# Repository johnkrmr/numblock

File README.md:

# Numblock #
A small 4x5 diy keypad to get into pcb design and custom keyboards.

## IMPORTANT ##
PCB not tested yet. There's no guarantee that it will work right now!  
Front panel needed to mount 3-pin switches. No files for that provided yet.  
Generally this README and the whole project is far away from being
complete.

## Features ##
- 4x5 keys (cherry mx compatible, hotswappable)
- compatible with variety of Adafruit ItsyBitsy boards:
	- 32u4 (3.3V 8MHz Version!)
	- M4
	- nRF52840
	- RP2040?
	- M0?
- up to 2 rotary encoders (optional)
- indicator RGB led (optional)
- RGB underglow (optional)
- RGB backlight (optional)
- i2c OLED-Display (optional)
- small 'prototyping' area with access to i2c, serial + some analog Pins

## Components ##
- PCB
- 20 1N4148W Diods (SOD123 package)
- 20 hotswap sockets for cherry mx compatible switches
- 20 cherry mx compatible switches (both 3 and 5 pin versions should
work)
- compatible ItsyBitsy controller (cf. features)
- 8 SK6812 mini *HW* RGB LEDs for underglow + top indicator led
- 20 SK6812 mini RGB LEDs for backlight
- 0.1μF 0805 capacitors for each RGB LED (cf. notes)
- up to 2 Alps EC11E rotary encoders
- i2c OLED display, [this
one](https://www.waveshare.com/wiki/0.91inch_OLED_Module) should fit perfectly
- front panel
- some sort of case or an extra back panel
- screws to hold the whole thing together
- rubber feet (otherwise typing won't be much fun)

## Notes ##
### Electronics ###
- 0.1μF capacitors are recommended according to the datasheet. There are many
designs without them. I do not know whether or not they are necessary.
- A resistor on the LED data line between the controller and the first led is
recommended. I forgot to add that on. Here as well many pcbs do not include
them. It should work. [Supposedly](https://learn.adafruit.com/adafruit-neopixel-uberguide/basic-connections) what could happen is that the first LED in the 'chain' gets fried every
once in a while.
- A wireless version could be achieved with the nRF52840 in combination with the [LiIon/LiPoly
Backpack](https://www.adafruit.com/product/2124).

### Software ###
- I experienced some form of 'ghosting' in the upper two rows when setting
columns to *high* and
reading from row pins with *internal pulldowns* (diodes
facing opposite way than shown in schematics). When holding 4
switches down in same row, the 5th one shows as constantly on or
continuously toggling. This does
not seam to appear when setting rows to *low* and reading from columns with *internal
pullups*. So I guess **use internal pullups** for scanning the matrix.

## Resources ##
- [Josef Adamcik's sofle
keyboard](https://josefadamcik.github.io/SofleKeyboard/)
- [KiCad Keyboard Tutorial](https://github.com/ruiqimao/keyboard-pcb-guide)

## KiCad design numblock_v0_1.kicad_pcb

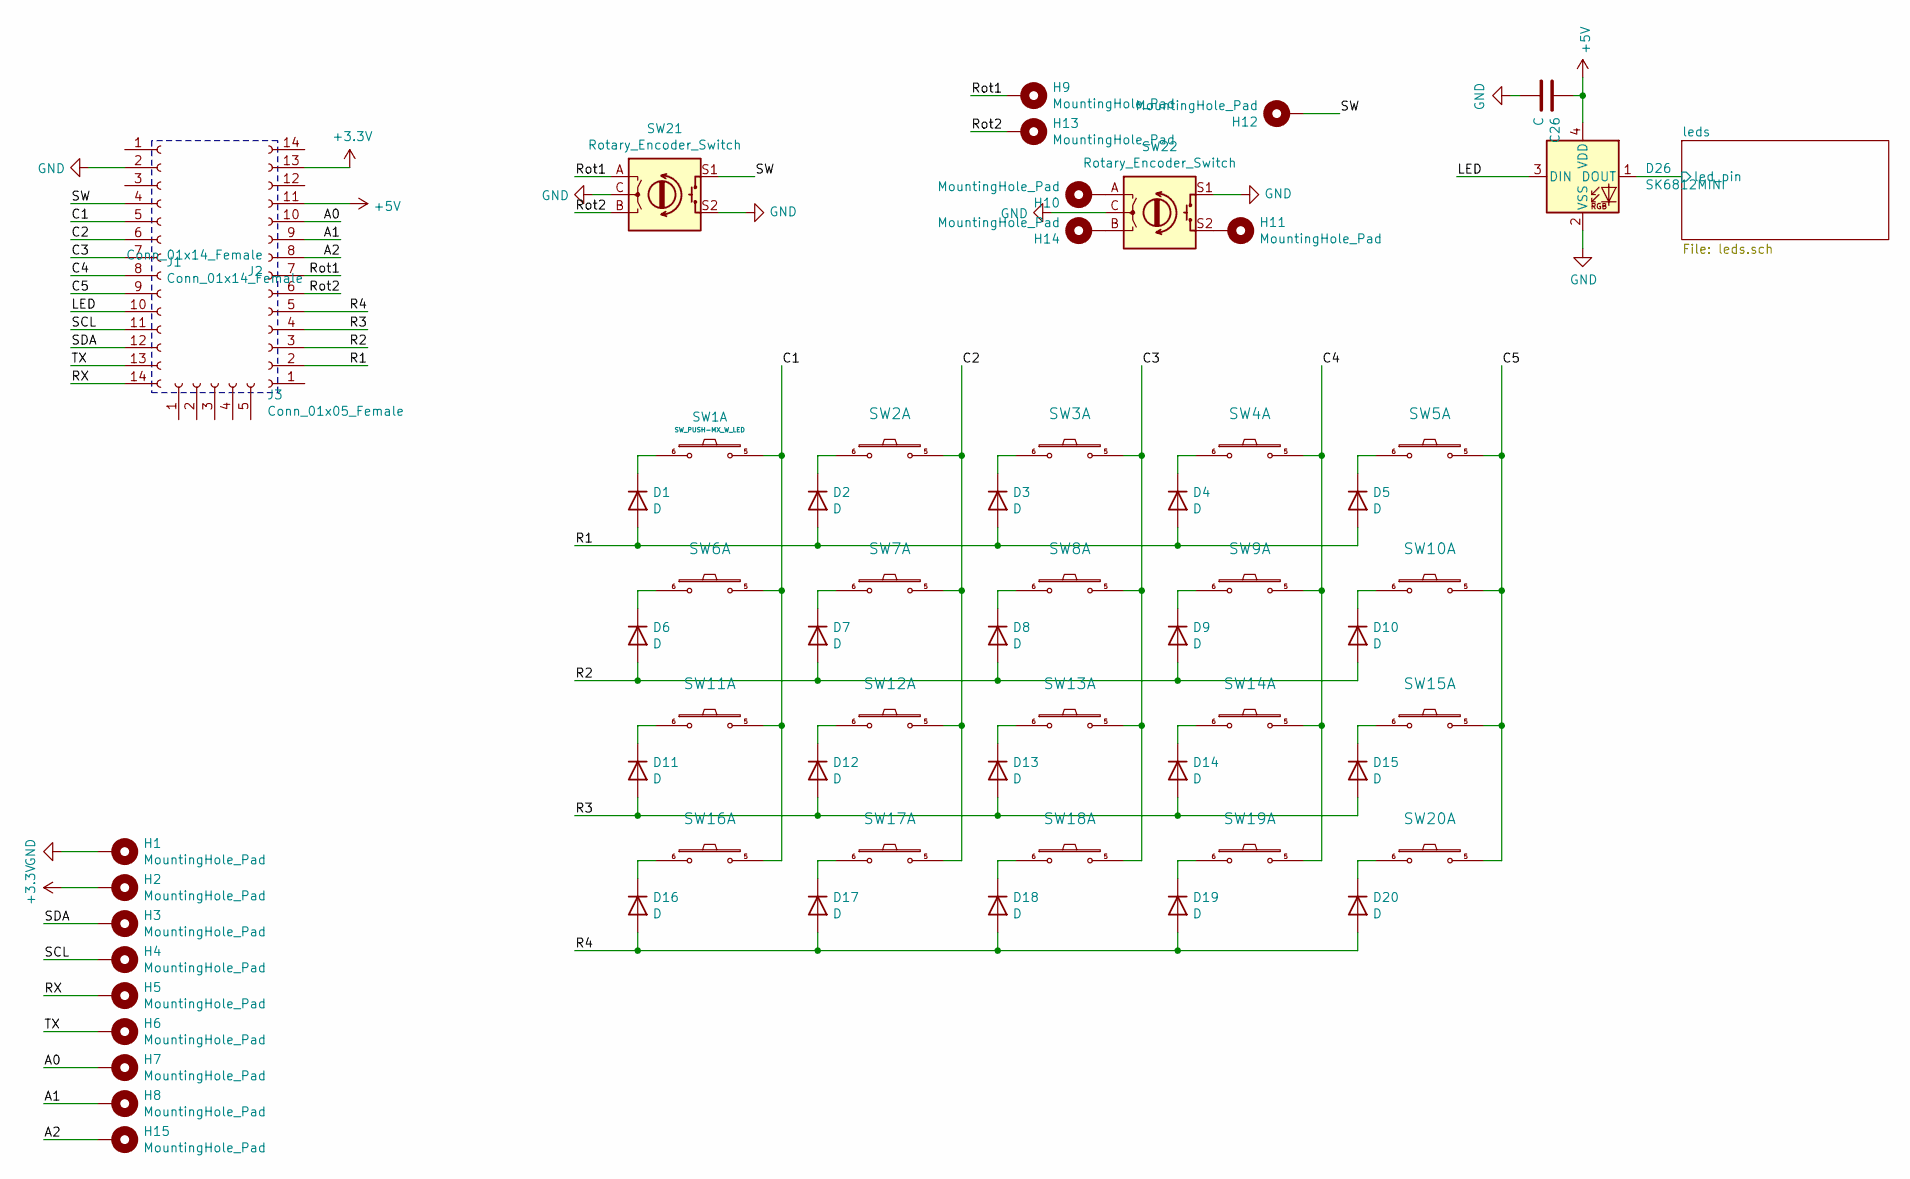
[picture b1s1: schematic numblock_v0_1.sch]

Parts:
C26: C; C_0805_2012Metric_Pad1.18x1.45mm_HandSolder
D1, D2, D3, D4, D5, D6, D7, D8, D9, D10, D11, D12, D13, D14, D15, D16, D17, D18, D19, D20: D; D_SOD-123
D26: SK6812MINI; LED_SK6812MINI_HS
H1, H2, H3, H4, H5, H6, H7, H8, H9, H10, H11, H12, H13, H14, H15: MountingHole_Pad; hole_30mil
J1, J2: Conn_01x14_Female; PinSocket_1x14_P2.54mm_Vertical
J3: Conn_01x05_Female; PinSocket_1x05_P2.54mm_Vertical
SW1, SW2, SW3, SW4, SW5, SW11, SW12, SW13, SW14, SW15: SW_PUSH-MX_W_LED; SK6812MINI_and_cherry_oneside_ledflipped
SW6, SW7, SW8, SW9, SW10, SW16, SW17, SW18, SW19, SW20: SW_PUSH-MX_W_LED; SK6812MINI_and_cherry_oneside
SW21: Rotary_Encoder_Switch; RotaryEncoder_Alps_EC11E-Switch_Vertical_H20mm_NoMountingHo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
SW22: Rotary_Encoder_Switch; RotaryEncoder_Alps_EC11E-Switch_Vertical_H20mm-keebio_modif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

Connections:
+3V3: H2.1, J2.13
+5V: C26.1, D26.4 (VDD), J2.11; also elsewhere on the board
/A0: H7.1, J2.10
/A1: H8.1, J2.9
/A2: H15.1, J2.8
/C1: J1.5, SW1.5, SW6.5, SW11.5, SW16.5
/C2: J1.6, SW2.5, SW7.5, SW12.5, SW17.5
/C3: J1.7, SW3.5, SW8.5, SW13.5, SW18.5
/C4: J1.8, SW4.5, SW9.5, SW14.5, SW19.5
/C5: J1.9, SW5.5, SW10.5, SW15.5, SW20.5
/LED: D26.3 (DIN), J1.10
/R1: D1.2 (A), D2.2 (A), D3.2 (A), D4.2 (A), D5.2 (A), J2.2
/R2: D6.2 (A), D7.2 (A), D8.2 (A), D9.2 (A), D10.2 (A), J2.3
/R3: D11.2 (A), D12.2 (A), D13.2 (A), D14.2 (A), D15.2 (A), J2.4
/R4: D16.2 (A), D17.2 (A), D18.2 (A), D19.2 (A), D20.2 (A), J2.5
/RX: H5.1, J1.14
/Rot1: H9.1, J2.7, SW21.A
/Rot2: H13.1, J2.6, SW21.B
/SCL: H4.1, J1.11
/SDA: H3.1, J1.12
/SW: H12.1, J1.4, SW21.S1
/TX: H6.1, J1.13
GND: C26.2, D26.2 (VSS), H1.1, J1.2, SW21.C, SW21.S2, SW22.C, SW22.S1; also elsewhere on the board
unnamed: D1.1 (K), SW1.6
unnamed: D2.1 (K), SW2.6
unnamed: D3.1 (K), SW3.6
unnamed: D4.1 (K), SW4.6
unnamed: D5.1 (K), SW5.6
unnamed: D6.1 (K), SW6.6
unnamed: D7.1 (K), SW7.6
unnamed: D8.1 (K), SW8.6
unnamed: D9.1 (K), SW9.6
unnamed: D10.1 (K), SW10.6
unnamed: D11.1 (K), SW11.6
unnamed: D12.1 (K), SW12.6
unnamed: D13.1 (K), SW13.6
unnamed: D14.1 (K), SW14.6
unnamed: D15.1 (K), SW15.6
unnamed: D16.1 (K), SW16.6
unnamed: D17.1 (K), SW17.6
unnamed: D18.1 (K), SW18.6
unnamed: D19.1 (K), SW19.6
unnamed: D20.1 (K), SW20.6
unnamed: H10.1, SW22.A
unnamed: H11.1, SW22.S2
unnamed: H14.1, SW22.B

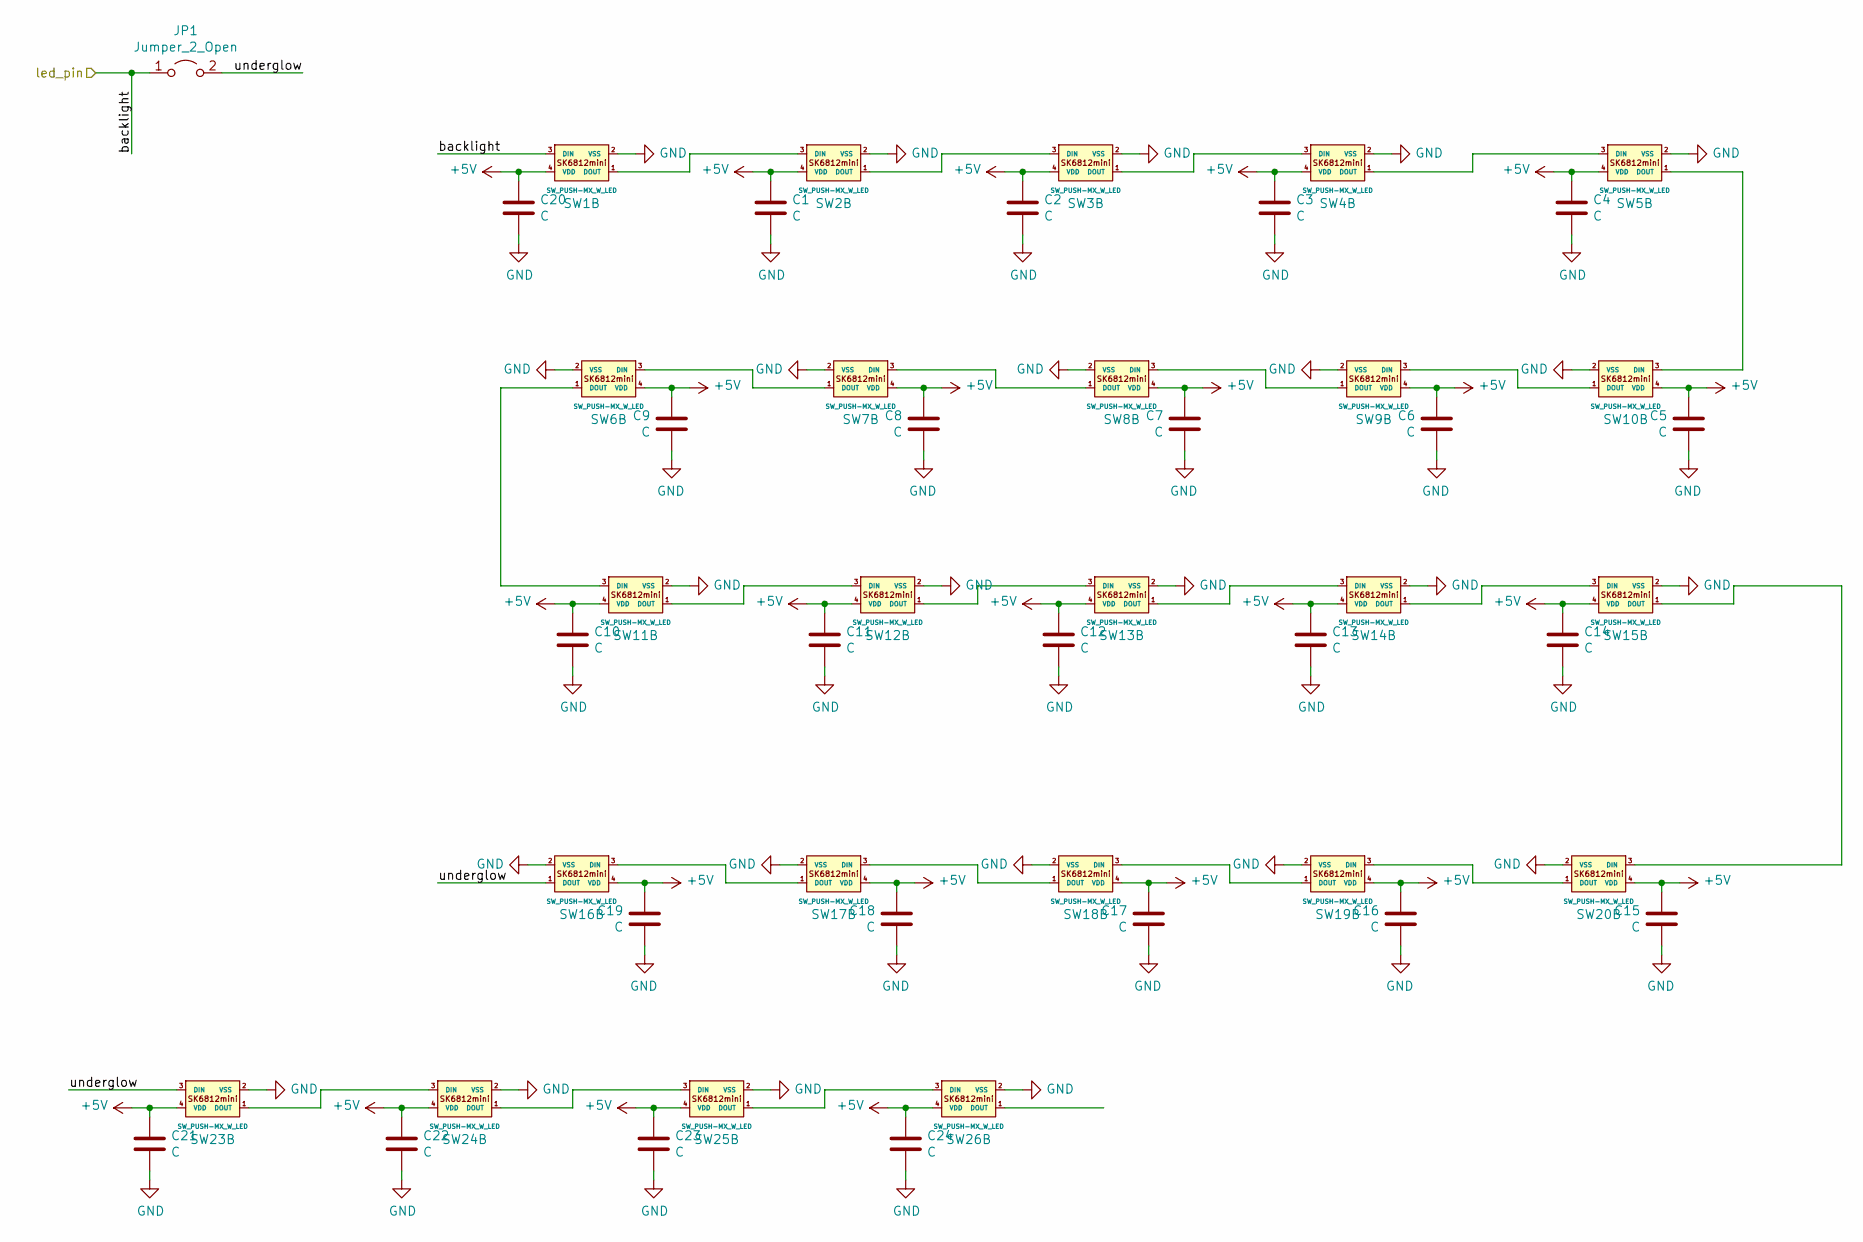
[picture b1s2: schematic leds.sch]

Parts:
C1, C2, C3, C4, C5, C6, C7, C8, C9, C10, C11, C12, C13, C14, C15, C16, C17, C18, C19, C20, C21, C22, C23, C24: C; C_0805_2012Metric_Pad1.18x1.45mm_HandSolder
JP1: Jumper_2_Open; SolderJumper-2_P1.3mm_Open_TrianglePad1.0x1.5mm
SW1, SW2, SW3, SW4, SW5, SW11, SW12, SW13, SW14, SW15, SW23, SW24, SW25, SW26: SW_PUSH-MX_W_LED; SK6812MINI_and_cherry_oneside_ledflipped
SW6, SW7, SW8, SW9, SW10, SW16, SW17, SW18, SW19, SW20: SW_PUSH-MX_W_LED; SK6812MINI_and_cherry_oneside

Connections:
+5V: C1.1, C2.1, C3.1, C4.1, C5.1, C6.1, C7.1, C8.1, C9.1, C10.1, C11.1, C12.1, C13.1, C14.1, C15.1, C16.1, C17.1, C18.1, C19.1, C20.1, C21.1, C22.1, C23.1, C24.1, SW1.4 (VDD), SW2.4 (VDD), SW3.4 (VDD), SW4.4 (VDD), SW5.4 (VDD), SW6.4 (VDD), SW7.4 (VDD), SW8.4 (VDD), SW9.4 (VDD), SW10.4 (VDD), SW11.4 (VDD), SW12.4 (VDD), SW13.4 (VDD), SW14.4 (VDD), SW15.4 (VDD), SW16.4 (VDD), SW17.4 (VDD), SW18.4 (VDD), SW19.4 (VDD), SW20.4 (VDD), SW23.4 (VDD), SW24.4 (VDD), SW25.4 (VDD), SW26.4 (VDD); also elsewhere on the board
GND: C1.2, C2.2, C3.2, C4.2, C5.2, C6.2, C7.2, C8.2, C9.2, C10.2, C11.2, C12.2, C13.2, C14.2, C15.2, C16.2, C17.2, C18.2, C19.2, C20.2, C21.2, C22.2, C23.2, C24.2, SW1.2 (VSS), SW2.2 (VSS), SW3.2 (VSS), SW4.2 (VSS), SW5.2 (VSS), SW6.2 (VSS), SW7.2 (VSS), SW8.2 (VSS), SW9.2 (VSS), SW10.2 (VSS), SW11.2 (VSS), SW12.2 (VSS), SW13.2 (VSS), SW14.2 (VSS), SW15.2 (VSS), SW16.2 (VSS), SW17.2 (VSS), SW18.2 (VSS), SW19.2 (VSS), SW20.2 (VSS), SW23.2 (VSS), SW24.2 (VSS), SW25.2 (VSS), SW26.2 (VSS); also elsewhere on the board
unnamed: SW1.1 (DOUT), SW2.3 (DIN)
unnamed: SW2.1 (DOUT), SW3.3 (DIN)
unnamed: SW3.1 (DOUT), SW4.3 (DIN)
unnamed: SW4.1 (DOUT), SW5.3 (DIN)
unnamed: SW6.3 (DIN), SW7.1 (DOUT)
unnamed: SW7.3 (DIN), SW8.1 (DOUT)
unnamed: SW8.3 (DIN), SW9.1 (DOUT)
unnamed: SW9.3 (DIN), SW10.1 (DOUT)
unnamed: SW5.1 (DOUT), SW10.3 (DIN)
unnamed: SW11.1 (DOUT), SW12.3 (DIN)
unnamed: SW6.1 (DOUT), SW11.3 (DIN)
unnamed: SW12.1 (DOUT), SW13.3 (DIN)
unnamed: SW13.1 (DOUT), SW14.3 (DIN)
unnamed: SW14.1 (DOUT), SW15.3 (DIN)
unnamed: SW15.1 (DOUT), SW20.3 (DIN)
unnamed: SW16.3 (DIN), SW17.1 (DOUT)
unnamed: SW17.3 (DIN), SW18.1 (DOUT)
unnamed: SW18.3 (DIN), SW19.1 (DOUT)
unnamed: SW19.3 (DIN), SW20.1 (DOUT)
unnamed: SW23.1 (DOUT), SW24.3 (DIN)
unnamed: SW24.1 (DOUT), SW25.3 (DIN)
unnamed: SW25.1 (DOUT), SW26.3 (DIN)

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
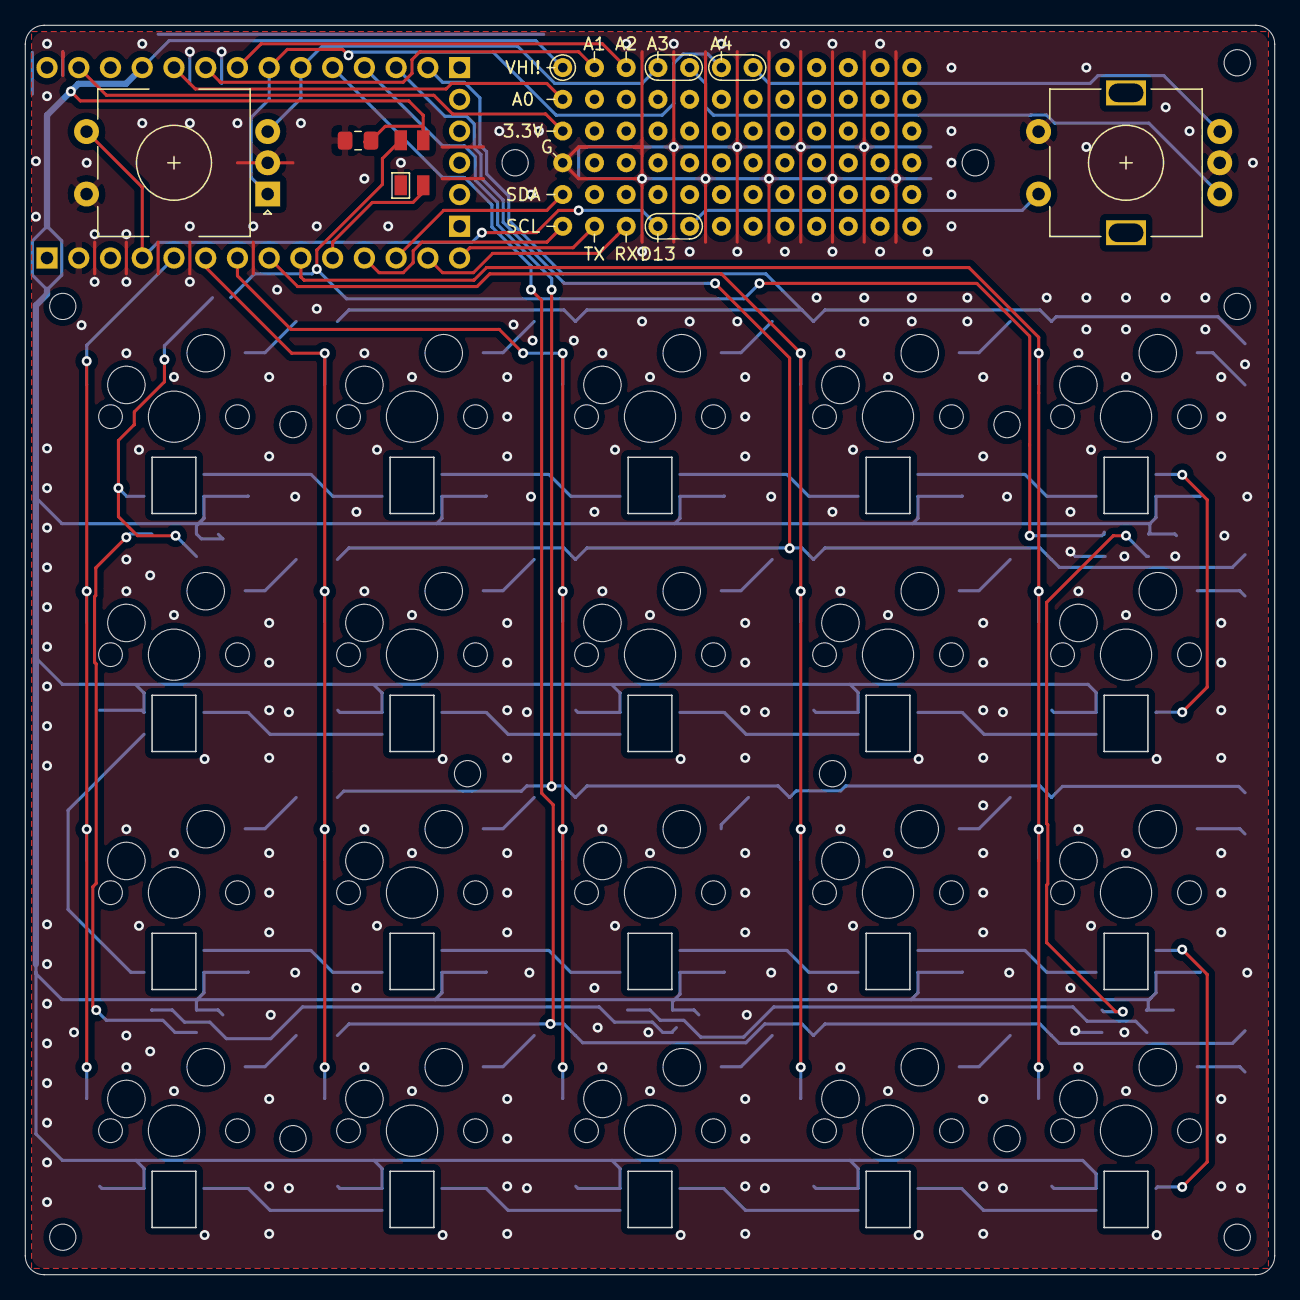
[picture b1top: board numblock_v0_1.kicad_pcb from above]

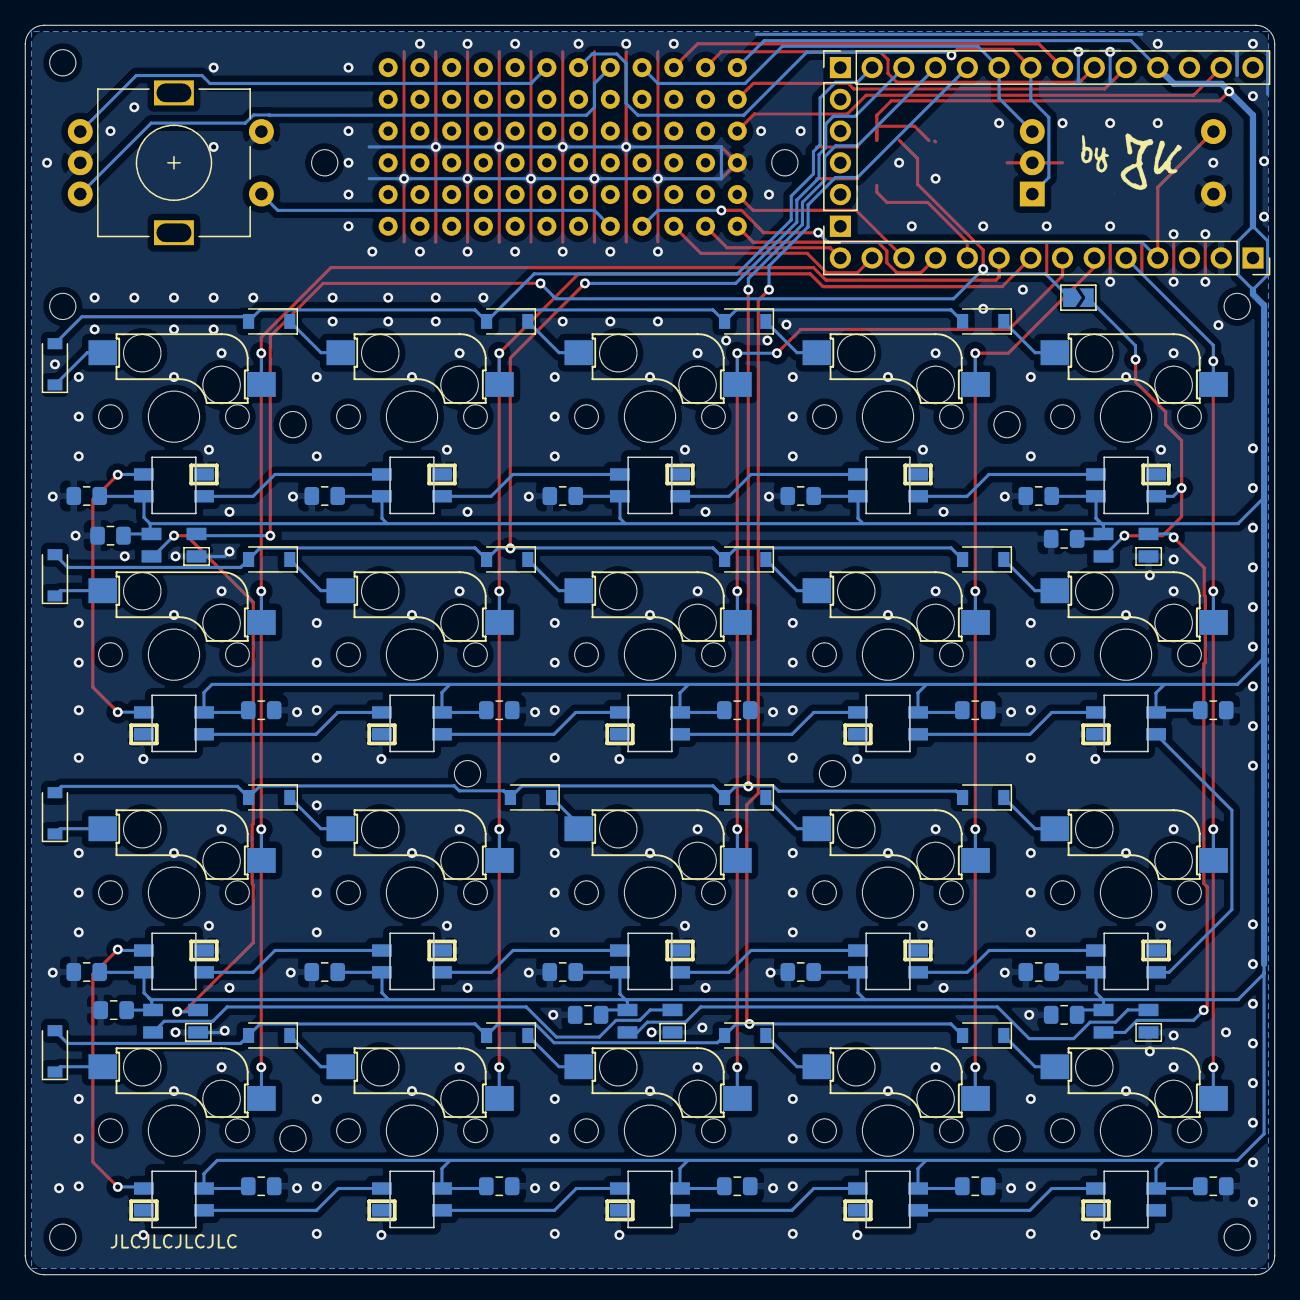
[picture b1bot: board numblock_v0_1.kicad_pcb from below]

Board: 2 copper layers, 100.0 x 100.0 mm, 106 parts (54 on the bottom side), 71 nets.

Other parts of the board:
C25: C; C_0805_2012Metric_Pad1.18x1.45mm_HandSolder
D21, D22, D23, D24, D25: SK6812MINI; LED_SK6812MINI_HS
TH1, TH1#2, TH1#3, TH1#4, TH1#5, TH1#6, TH1#7, TH1#8, TH1#9, TH1#10, TH1#11, TH1#12, TH1#13: HOLE; MountingHole_2.1mm

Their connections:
+5V: C25.1, D21.4, D22.4, D23.4, D24.4, D25.4; also elsewhere on the board
GND: C25.2, D21.2, D22.2, D23.2, D24.2, D25.2; also elsewhere on the board
unnamed: D21.1, D22.3
unnamed: D22.1, D23.3
unnamed: D23.1, D24.3
unnamed: D24.1, D25.3

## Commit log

2021-05-08 Initialer Commit
2021-05-08 Fixed missing gnd connections
2021-05-11 kinda done, about to add jumpers for rot. enc.
2021-05-11 done for tonight
2021-05-14 about to add underglow
2021-05-14 added top led and oled display support
2021-05-14 fixed display position
2021-05-14 moved display down
2021-05-14 fixed backlight leds; added holes
2021-05-14 mounting holes added
2021-05-22 replaced plated mountig holes to unplated; final touches before placing order
2021-05-22 README added (not complete yet)
2021-05-22 Added required components and some more info
2021-05-22 added pcb renders
2021-05-22 removed html images
2021-05-23 added wireless note; fixed mistake
2021-06-05 Added software notes
2022-04-21 add firmware + test firmware
2022-04-22 fix minor issue
2022-04-22 add ROWCOL mode
